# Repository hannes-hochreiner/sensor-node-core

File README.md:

# Sensor Node Core

This is another take on the sensor node theme.
I am planning on separating the core form the actual sensor.
The core will contain the micro-controller (incl. debug connector and reset button), radio (incl. antenna), and battery, as well as a connector providing power, SPI, I2C, and GPIOs.

## Main parts

### STM32
  * STMicroelectronics: STM32L021K4T6
  * Digi-Key: [497-17903-ND](https://www.digikey.de/product-detail/de/stmicroelectronics/STM32L021K4T6/497-17903-ND)
  * [datasheet](http://www.st.com/content/ccc/resource/technical/document/datasheet/86/a6/5f/95/33/50/4e/d6/DM00206858.pdf/files/DM00206858.pdf/jcr:content/translations/en.DM00206858.pdf)
  * Sleep Current: 0.54 µA
  * Price: 1.87

### RFM98
  * Seeed Technology Co., Ltd: 109990165
  * Digi-Key: [1597-1491-ND](https://www.digikey.de/product-detail/de/seeed-technology-co-ltd/109990165/1597-1491-ND)
  * [datasheet](https://github.com/SeeedDocument/RFM95-98_LoRa_Module/blob/master/RFM95_96_97_98_DataSheet.pdf)
  * Sleep Current: 0.2 µA
  * Price: 6.05

### Box
  * Hammond Manufacturing: 1551JGY
  * Digi-Key: [HM1133-ND](https://www.digikey.de/product-detail/de/hammond-manufacturing/1551JGY/HM1133-ND/2094871)
  * [Datasheet](http://www.hammondmfg.com/pdf/1551J.pdf)
  * Price: 2.09

### SWD Connector
  * CNC Tech: 3220-10-0100-00
  * Digi-Key: [1175-1627-ND](https://www.digikey.de/product-detail/en/cnc-tech/3220-10-0100-00/1175-1627-ND/3883661)
  * Price: 0.51

### 10-pin Sensor Connector
  * Harwin Inc.: M50-3150542R
  * Digi-Key: [952-3493-1-ND](https://www.digikey.de/product-detail/en/harwin-inc/M50-3150542R/952-3493-1-ND/6797677)
  * [Datasheet](https://cdn.harwin.com/pdfs/M50-315R.pdf)
  * Price: 2.27

### Coin Cell Holder
  * MPD (Memory Protection Devices): BU2032-1-G
  * Digi-Key: [BU2032-1-G-ND](https://www.digikey.de/product-detail/en/mpd-memory-protection-devices/BU2032-1-G/BU2032-1-G-ND/2439519)
  * [Datasheet](http://www.memoryprotectiondevices.com/datasheets/BU2032-1-G-datasheet.pdf)
  * Price: 0.89

### Button
  * TE Connectivity ALCOSWITCH Switches: 1825910-6
  * Digi-Key: [450-1650-ND](https://www.digikey.de/product-detail/en/te-connectivity-alcoswitch-switches/1825910-6/450-1650-ND/1632536)
  * [Datasheet](https://www.te.com/commerce/DocumentDelivery/DDEController?Action=srchrtrv&DocNm=1825910&DocType=Customer+Drawing&DocLang=English)
  * Price: 0.09

## Price

Estimate: about 20 EUR

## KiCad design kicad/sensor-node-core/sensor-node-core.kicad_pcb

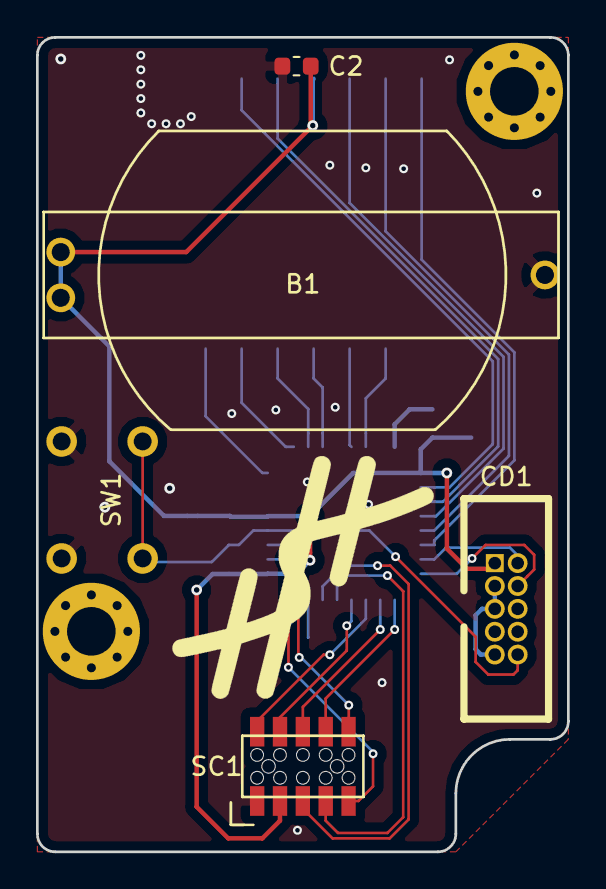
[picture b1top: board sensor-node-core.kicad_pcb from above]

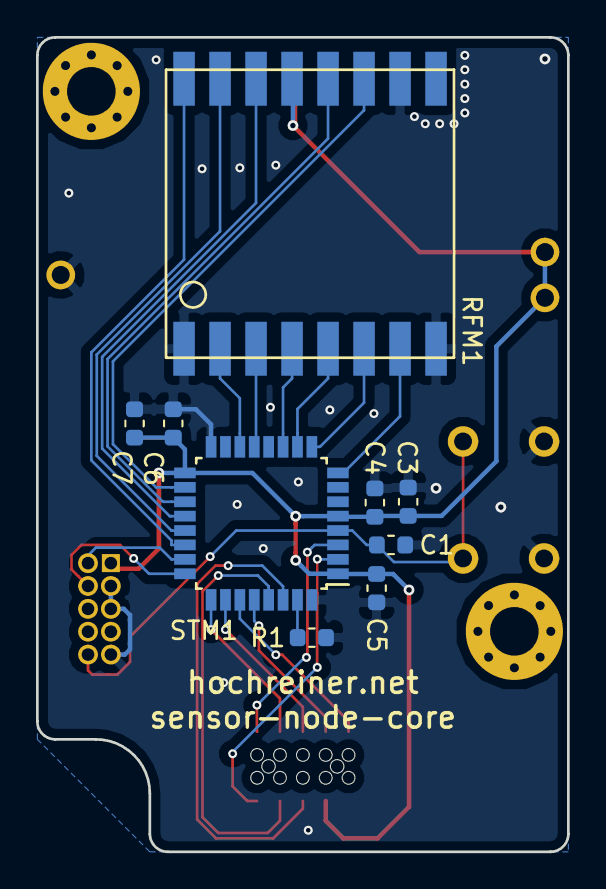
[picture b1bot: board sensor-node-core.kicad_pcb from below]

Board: 2 copper layers, 29.5 x 45.2 mm, 14 parts (9 on the bottom side), 25 nets.

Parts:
B1: BU2032-1-G
C1, C2, C4, C5, C6: 0.1µF; C_0603_1608Metric
C3: 1µF; C_0603_1608Metric
C7: 10µF; C_0603_1608Metric
CD1: CORTEX-DEBUG
R1: 10k; C_0603_1608Metric
RFM1: RFM98
SC1: Sensor-Connector; M50-3150542R
STM1: STM32L021K4T6; LQFP-32_7x7mm_P0.8mm
SW1: SW_Push; switch

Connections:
/3V3: B1.1, C2.1, C3.1, C4.1, C5.2, C6.1, C7.1, CD1.1, RFM1.13, SC1.3, STM1.1, STM1.5, STM1.17
/RFM_DIO0: RFM1.14, STM1.20
/RFM_DIO1: RFM1.15, STM1.21
/RFM_DIO2: RFM1.16, STM1.22
/RFM_DIO3: RFM1.11, STM1.18
/RFM_DIO4: RFM1.12, STM1.19
/RFM_DIO5: RFM1.7, STM1.8
/RFM_RESET: RFM1.6, STM1.9
/RFM_SPI_CLK: RFM1.4, STM1.11
/RFM_SPI_MISO: RFM1.2, STM1.14
/RFM_SPI_MOSI: RFM1.3, STM1.13
/SEN_GPIO_1: SC1.9, STM1.2
/SEN_GPIO_2: SC1.10, STM1.3
/SEN_I2C_SCL: SC1.7, STM1.29
/SEN_I2C_SDA: SC1.5, STM1.30
/SEN_SPI_CLK: SC1.6, STM1.26
/SEN_SPI_MISO: SC1.2, STM1.27
/SEN_SPI_MOSI: SC1.4, STM1.28
/SWD_CLK: CD1.4, STM1.24
/SWD_IO: CD1.2, STM1.23
/~RFM_SPI_CS: RFM1.5, STM1.10
/~SEN_SPI_CS: SC1.8, STM1.25
/~SWD_RST: C1.1, CD1.10, STM1.4, SW1.2
GND: B1.2, C1.2, C2.2, C3.2, C4.2, C5.1, C6.2, C7.2, CD1.3, CD1.5, CD1.9, R1.2, RFM1.1, RFM1.8, RFM1.10, SC1.1, STM1.16, STM1.32, SW1.1
unnamed: R1.1, STM1.31

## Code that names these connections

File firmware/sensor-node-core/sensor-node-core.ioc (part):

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Mcu.Name=STM32L021K4Tx
Mcu.Package=LQFP32
Mcu.UserName=STM32L021K4Tx
PA10.GPIOParameters=GPIO_Label
PA10.GPIO_Label=RFM_GPIO_0
PA10.Signal=GPIO_Input
PA11.GPIOParameters=GPIO_Label
PA11.GPIO_Label=RFM_GPIO_1
PA11.Signal=GPIO_Input
PA12.GPIOParameters=GPIO_Label
PA12.GPIO_Label=RFM_GPIO_2
PA12.Signal=GPIO_Input
PA13.Mode=Serial_Wire
PA13.Signal=SYS_SWDIO
PA14.Mode=Serial_Wire
PA14.Signal=SYS_SWCLK
PA15.GPIOParameters=GPIO_Label
PA15.GPIO_Label=SEN_SPI_NCS
PA15.Signal=GPIO_Input
PA2.GPIOParameters=GPIO_Label
PA2.GPIO_Label=RFM_GPIO_5
PA2.Signal=GPIO_Input
PA3.GPIOParameters=GPIO_Label
PA3.GPIO_Label=RFM_RESET
PA3.Signal=GPIO_Output
PA4.Mode=NSS_Signal_Hard_Input
PA4.Signal=SPI1_NSS
PA5.Mode=Full_Duplex_Master
PA5.Signal=SPI1_SCK
PA7.Mode=Full_Duplex_Master
PA7.Signal=SPI1_MOSI
PA8.GPIOParameters=GPIO_Label
PA8.GPIO_Label=RFM_GPIO_3
PA8.Signal=GPIO_Input
PA9.GPIOParameters=GPIO_Label
PA9.GPIO_Label=RFM_GPIO_4
PA9.Signal=GPIO_Input
PB0.Mode=Full_Duplex_Master
PB0.Signal=SPI1_MISO
PB3.GPIOParameters=GPIO_Label
PB3.GPIO_Label=SEN_SPI_CLK
PB3.Signal=GPIO_Input
PB4.GPIOParameters=GPIO_Label
PB4.GPIO_Label=SEN_SPI_MISO
PB4.Signal=GPIO_Input
PB5.GPIOParameters=GPIO_Label
PB5.GPIO_Label=SEN_SPI_MOSI
PB5.Signal=GPIO_Output
PB6.Mode=I2C
PB6.Signal=I2C1_SCL
PB7.Mode=I2C
PB7.Signal=I2C1_SDA
PC14-OSC32_IN.GPIOParameters=GPIO_Label
PC14-OSC32_IN.GPIO_Label=SEN_GPIO_1
PC14-OSC32_IN.Signal=GPIO_Input
PC15-OSC32_OUT.GPIOParameters=GPIO_Label
PC15-OSC32_OUT.GPIO_Label=SEN_GPIO_2
PC15-OSC32_OUT.Signal=GPIO_Input
RCC.HSE_VALUE=8000000
RCC.SYSCLKFreq_VALUE=2097000
board=custom

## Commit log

2018-11-28 listed main parts
2018-11-29 added footprints
2018-11-29 added schematic
2018-11-30 updated switch model and layout
2018-11-30 added firmware folder and routing
2018-11-30 added label and logo
2018-12-01 added a rendering of the board
2019-01-19 added images of the sensor node core
2019-01-27 added more pictures
